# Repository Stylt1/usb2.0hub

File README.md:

View this project on [CADLAB.io](https://cadlab.io/project/30472). 

# usb2.0hub

3D Renders:

## 🚀 USB 2.0 High-Speed Hub

This project is a custom-designed **4-port USB 2.0 hub** built around the WCH CH334F controller. It is optimized for stable data transmission and reliable power distribution.

### ⚡ Core Specifications
* **Protocol:** USB 2.0 High-Speed
* **Transfer Rate:** Up to 480 Mbps
* **Controller IC:** CH334F
* **Upstream Port:** 1x USB [Type-C] (Connection to PC/Host)
* **Downstream Ports:** 4x USB [Type-A] (Connection for peripherals)

### 🛠️ PCB Design & Stackup
To ensure signal integrity and proper 90Ω differential impedance for the USB data lines, the board is designed as a **4-layer PCB**. 

**Layer Stackup:**
1. **Top Layer:** Signal (Main high-speed routing and components)
2. **Inner Layer 1:** GND Plane (Solid ground reference)
3. **Inner Layer 2:** Power Plane (Power distribution)
4. **Bottom Layer:** Second Signal (Low-speed routing and signal crossovers)

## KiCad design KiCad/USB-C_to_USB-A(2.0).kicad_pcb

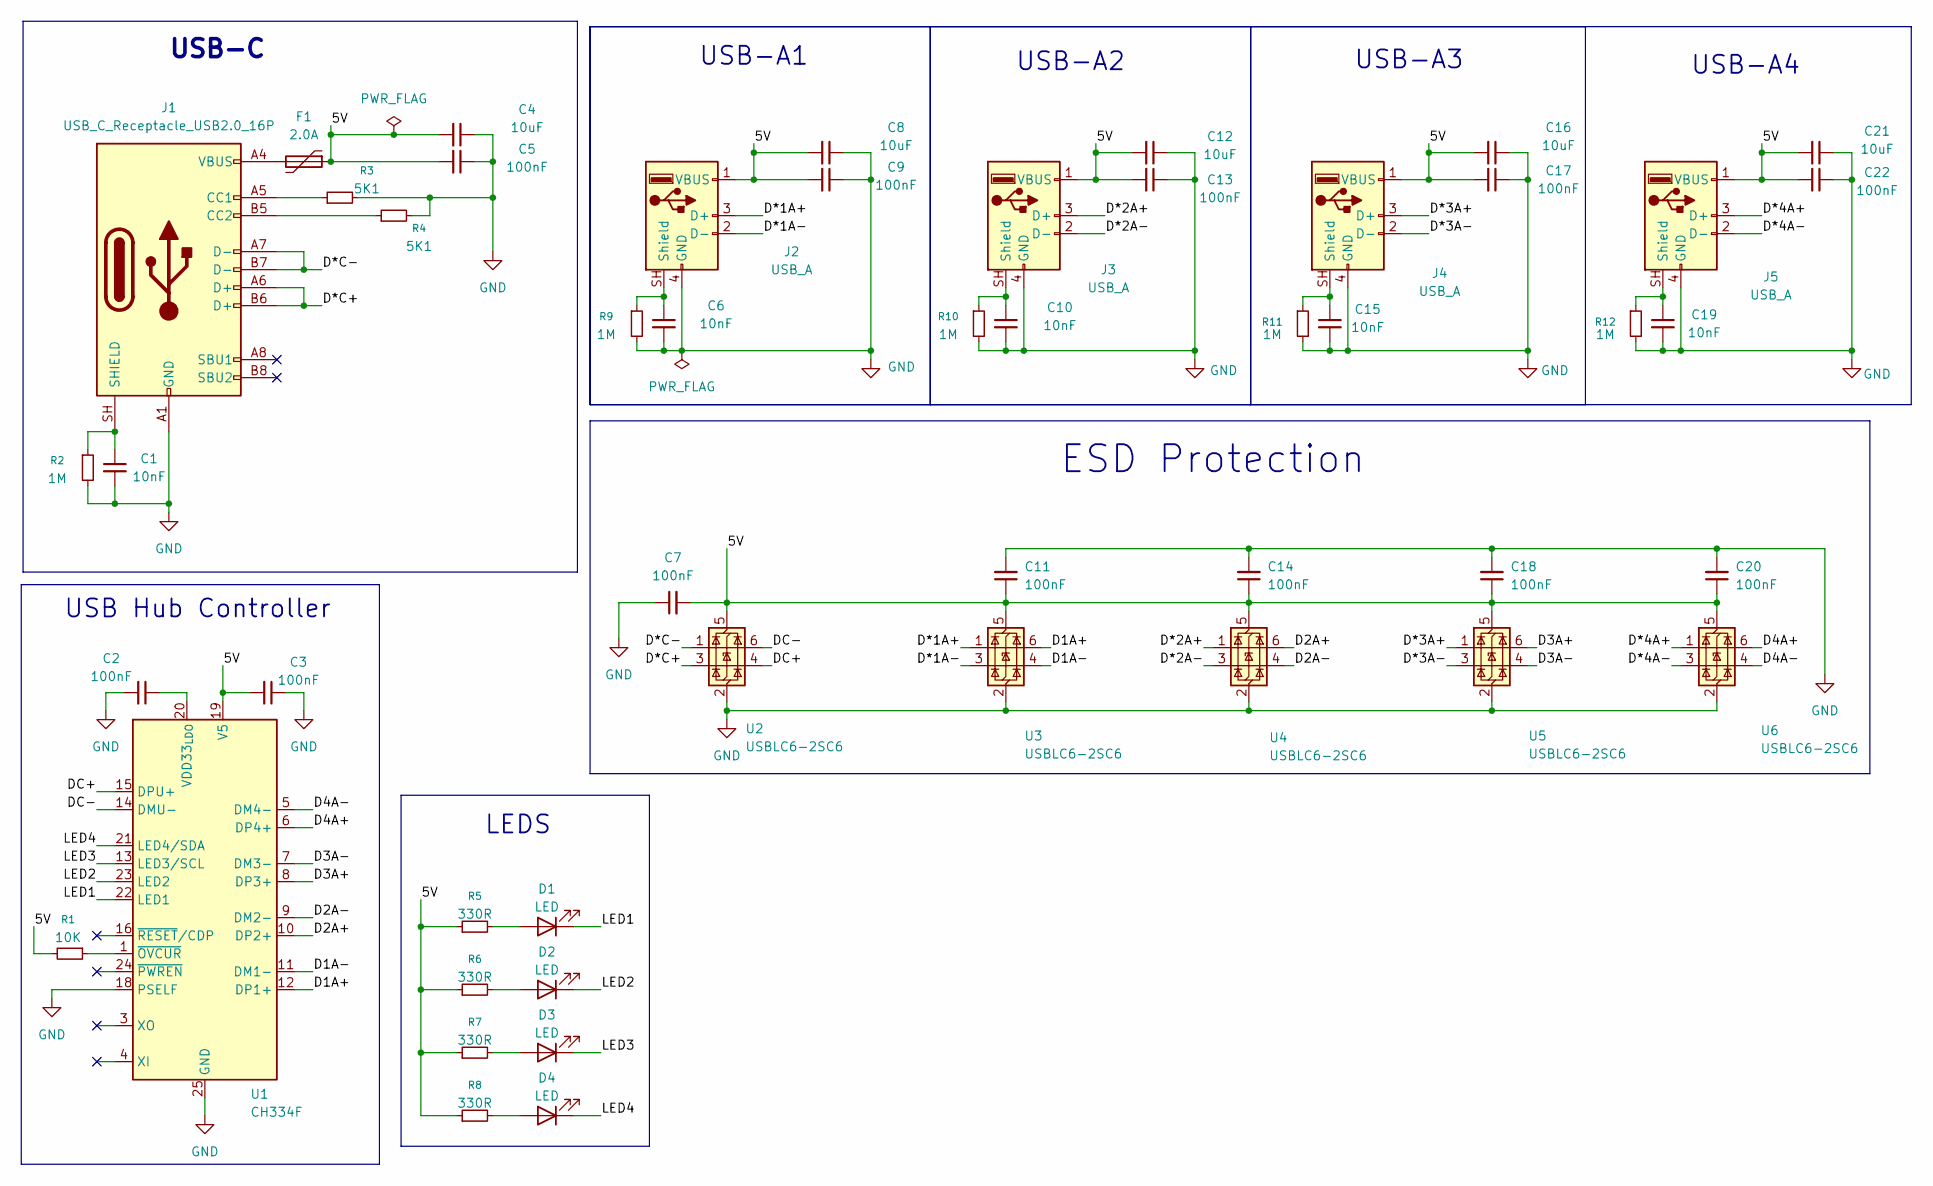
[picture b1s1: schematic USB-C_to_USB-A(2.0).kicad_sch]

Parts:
C1, C6, C10, C15, C19: 10nF; C_0603_1608Metric
C2, C3, C5, C7, C9, C11, C13, C14, C17, C18, C20, C22: 100nF; C_0603_1608Metric
C4, C8, C12, C16, C21: 10uF; C_1206_3216Metric
D1, D2, D3, D4: LED; LED_0603_1608Metric
F1: 2.0A; Fuse_1210_3225Metric
J1: USB_C_Receptacle_USB2.0_16P; USB_C_Receptacle_XKB_U262-16XN-4BVC11
J2, J3, J4, J5: USB_A; USB_A_Molex_48037-2200_Horizontal
R1: 10K; R_0603_1608Metric
R2, R9, R10, R11, R12: 1M; R_0603_1608Metric
R3, R4: 5K1; R_0603_1608Metric
R5, R6, R7, R8: 330R; R_0603_1608Metric
U1: CH334F; QFN-24-1EP_4x4mm_P0.5mm_EP2.7x2.7mm
U2, U3, U4, U5, U6: USBLC6-2SC6; SOT-23-6

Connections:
/5V: C3.2, C4.2, C5.2, C7.2, C8.2, C9.2, C11.1, C12.2, C13.2, C14.1, C16.2, C17.2, C18.1, C20.1, C21.2, C22.2, F1.1, J2.1 (VBUS), J3.1 (VBUS), J4.1 (VBUS), J5.1 (VBUS), R1.2, R5.1, R6.1, R7.1, R8.1, U1.19 (V5), U2.5 (VBUS), U3.5 (VBUS), U4.5 (VBUS), U5.5 (VBUS), U6.5 (VBUS)
/D1A+: U1.12 (DP1+), U3.6 (I/O1)
/D1A-: U1.11 (DM1-), U3.4 (I/O2)
/D2A+: U1.10 (DP2+), U4.6 (I/O1)
/D2A-: U1.9 (DM2-), U4.4 (I/O2)
/D3A+: U1.8 (DP3+), U5.6 (I/O1)
/D3A-: U1.7 (DM3-), U5.4 (I/O2)
/D4A+: U1.6 (DP4+), U6.6 (I/O1)
/D4A-: U1.5 (DM4-), U6.4 (I/O2)
/D*1A+: J2.3 (D+), U3.1 (I/O1)
/D*1A-: J2.2 (D-), U3.3 (I/O2)
/D*2A+: J3.3 (D+), U4.1 (I/O1)
/D*2A-: J3.2 (D-), U4.3 (I/O2)
/D*3A+: J4.3 (D+), U5.1 (I/O1)
/D*3A-: J4.2 (D-), U5.3 (I/O2)
/D*4A+: J5.3 (D+), U6.1 (I/O1)
/D*4A-: J5.2 (D-), U6.3 (I/O2)
/D*C+: J1.A6 (D+), J1.B6 (D+), U2.3 (I/O2)
/D*C-: J1.A7 (D-), J1.B7 (D-), U2.1 (I/O1)
/DC+: U1.15 (DPU+), U2.4 (I/O2)
/DC-: U1.14 (DMU-), U2.6 (I/O1)
/LED1: D1.1 (K), U1.22 (LED1)
/LED2: D2.1 (K), U1.23 (LED2)
/LED3: D3.1 (K), U1.13 (LED3/SCL)
/LED4: D4.1 (K), U1.21 (LED4/SDA)
GND: C1.2, C2.2, C3.1, C4.1, C5.1, C6.2, C7.1, C8.1, C9.1, C10.2, C11.2, C12.1, C13.1, C14.2, C15.2, C16.1, C17.1, C18.2, C19.2, C20.2, C21.1, C22.1, J1.A1 (GND), J1.A12 (GND), J1.B1 (GND), J1.B12 (GND), J2.4 (GND), J3.4 (GND), J4.4 (GND), J5.4 (GND), R2.2, R3.2, R4.2, R9.2, R10.2, R11.2, R12.2, U1.18 (PSELF), U1.25 (GND), U2.2 (GND), U3.2 (GND), U4.2 (GND), U5.2 (GND), U6.2 (GND)
unnamed: D1.2 (A), R5.2
unnamed: D2.2 (A), R6.2
unnamed: D3.2 (A), R7.2
unnamed: D4.2 (A), R8.2
unnamed: F1.2, J1.A4 (VBUS), J1.A9 (VBUS), J1.B4 (VBUS), J1.B9 (VBUS)
unnamed: J1.A5 (CC1), R3.1
unnamed: J1.B5 (CC2), R4.1
unnamed: C1.1, J1.SH (SHIELD), R2.1
unnamed: C6.1, J2.SH (Shield), R9.1
unnamed: C10.1, J3.SH (Shield), R10.1
unnamed: C15.1, J4.SH (Shield), R11.1
unnamed: C19.1, J5.SH (Shield), R12.1
unnamed: C2.1, U1.20 (VDD33_{LDO})
unnamed: R1.1, U1.1 (~OVCUR)

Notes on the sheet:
USB-A3
LEDS
USB-A2
ESD Protection
USB-A4
USB-C
USB Hub Controller
USB-A1

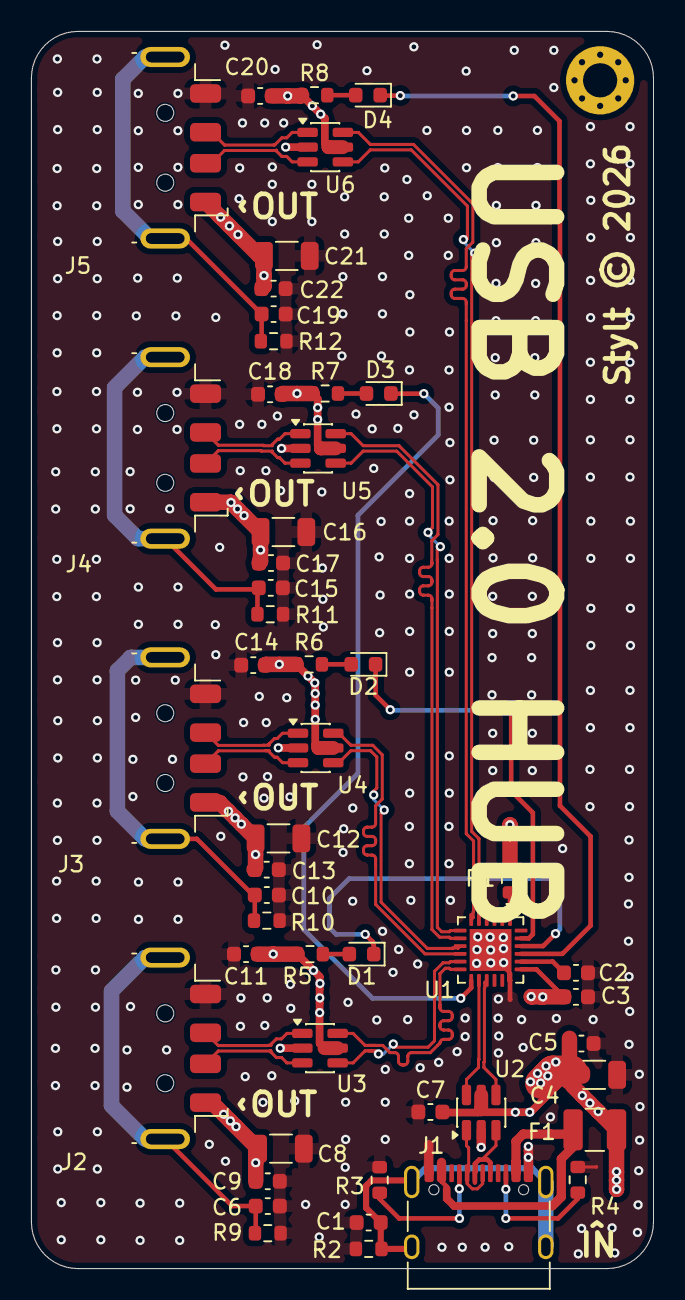
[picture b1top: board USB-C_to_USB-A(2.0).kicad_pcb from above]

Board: 4 copper layers, 40.1 x 79.8 mm, 50 parts (0 on the bottom side), 40 nets.

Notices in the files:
KiCad/USB-C_to_USB-A(2.0).kicad_pcb:
Stylt © 2026
